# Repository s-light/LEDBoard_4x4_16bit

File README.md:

<!--lint disable maximum-line-length-->
<!--lint disable list-item-spacing-->
<!--lint disable list-item-indent-->

# LED-Board 4x4 16bit

a LED-Matrix Board that can be combined seamlessly to bigger areas.  
It uses the [TI TLC5971](http://www.ti.com/product/TLC5971) Constant-Current LED-Driver Chip with 16bit dimming resolution.  

The [original](https://github.com/s-light/LEDBoard_4x4_16bit/tree/Nichia_NSSM032A) LED-footprint was for [Nichia NSSM032A](http://www.nichia.co.jp/en/product/led_product_data.html?type=%27NSSM032A%27) RGB-LED.
Back in 2017 on of the brightest *low power* SMD LEDs in this size -
They are only available as full reel directly from Nichia.

so there is a [second branch](https://github.com/s-light/LEDBoard_4x4_16bit/tree/Nichia_NSSM124D) with the LED-Type changed to [Nichia NSSM124D](http://www.nichia.co.jp/en/product/led_product_data.html?type=%27NSSM124D%27) -
these are [available as cut-tape from an distributor](http://www.leds.de/en/Ordinary-LEDs/SMD-LEDs/Nichia-SMD-LED-RGB-NSSM124DT.html).

latest addition is a [branch with TLC5971*PWP* driver chips](https://github.com/s-light/LEDBoard_4x4_16bit/tree/TLC5971PWP) -
this is the same chip but in an HTSSOP-20 housing -
that is easier to solder by hand.
--> no hot air / reflow oven necessary, but recommend.

## Project-Status
- received first Batch ([Release V1.0.0](https://github.com/s-light/LEDBoard_4x4_16bit/releases/tag/v1.0))
- received second Batch ([Release V3.0.1](https://github.com/s-light/LEDBoard_4x4_16bit/tree/v3.0.1))
- 11 PCB's assembled  
  10 working :sun_with_face:  
  first solder board not working - has a short between VCC and GND (to be checked)
- all needed heavy rework: stencil has to big openings - this gives a bunch of bridges at QFN 0,5mm Pin-Pitch IC's
- had some problems with the first reflow oven used - you need enough heat from the bottom to solder correctly.
- made some picture from first assembly: [gallery](./doc/gallery.md)
- ~~fix pads that are to small for hand-soldering~~ done
- ~~order updated PCB's~~ done
- ~~solder some more boards~~ done (total: ~60)
- ~~order screws at [Wegertseder](https://www.wegertseder.com/ArticleDetails.aspx?AKNUM=2588)~~ done
- updated KiCad files to new version.

### TODO
- order Heat Sink with machining and Thermal Foil from [Fischer Elektronik](http://www.fischerelektronik.de/web_fischer/de_DE/K%C3%BChlk%C3%B6rper/B01/K%C3%BChlk%C3%B6rper%20f%C3%BCr%20PGA/PR/ICKPGA14x14x12_/$productCard/parameters/index.xhtml)
- add some more mounting layouts to [LEDBoard_Layouts](https://github.com/s-light/LEDBoard_Layouts)
- take some more pictures

## Technical Information
there are groups of 4 LEDs that are controlled by one TLC5971.  
every controller chip has 12 ConstantCurrent outputs. so every LED is controllable individual.

you need to create a mapping to linearize the order:  

| X/Y   | 0        | 1        | 2        | 3        |
| :---- | :------- | :------- | :------- | :------- |
| **0** | IC1 LED1 | IC1 LED2 | IC2 LED1 | IC2 LED2 |
| **1** | IC1 LED3 | IC1 LED4 | IC2 LED3 | IC2 LED4 |
| **2** | IC3 LED1 | IC3 LED2 | IC4 LED1 | IC4 LED2 |
| **3** | IC3 LED3 | IC3 LED4 | IC4 LED3 | IC4 LED4 |

example for c++ / arduino
```c++
const uint8_t channel_position_map[4][4] = {
    { 0,  1,  4,  5},
    { 2,  3,  6,  7},
    { 8,  9, 12, 13},
    {10, 11, 14, 15},
};
```

### HW
- PCB size: 40x40x18mm
- pixel-pitch: 10mm
- 3.8V..5.5V
- <= 1A (maximum)

### BOM
there is the raw exported BOM at [export/BOM/LEDBoard_4x4_16bit_BOM.csv](export/BOM/LEDBoard_4x4_16bit_BOM.csv) and an modified LibreOffice Calc file with ordering and Price calculations at [doc/LEDBoard_4x4_16bit_PriceCalculation_Ordering](doc/LEDBoard_4x4_16bit_PriceCalculation_Ordering.csv) (link points to exported csv as preview)

### controlling

#### Micro Controller / Arduino
there are some Arduino Libraries out there that can generate the correct protocol.
My Favorite is [ulrichstern/Tlc59711](https://github.com/ulrichstern/Tlc59711)

i have made a [simple arduino sketch](https://github.com/s-light/LEDBoard_4x4_16bit_HWTest) that uses the mentioned library to test the Boards during production.

#### embedded linux boards
Additionally you can use a embedded Linux board with an SPI output to drive them.
I have successfully implemented the protocol in my fork of OLA.
(TODO: Link and explain OLA setup)

there are also other python libraries out there.
(TODO: test some of theme and link here)

### power & signal connections
theoretically calculate with about 1A@5V for every Board.
Supply Voltage (VCC) should be 3,8V..5,5V - If possible use the lower end. so no extra heat is generated in the driver IC.

for the control-signal there are an input and output 3pin 2,54mm connector:
1. Data
1. Clock
1. GND

for the power there are 3x2pin 2,54mm connector positions.
so you could daisy-chain power also - but be aware the pcb-traces can handle an absolute maximum of 3,5A. So i would recommend only 1 or maximum 2 daisy-chained boards.

## KiCad Version
```text
Application: KiCad

Version: 5.99.0-unknown-652a59b78~104~ubuntu20.04.1, release build

Libraries:
	wxWidgets 3.0.4
	libcurl/7.68.0 OpenSSL/1.1.1f zlib/1.2.11 brotli/1.0.7 libidn2/2.2.0 libpsl/0.21.0 (+libidn2/2.2.0) libssh/0.9.3/openssl/zlib nghttp2/1.40.0 librtmp/2.3

Platform: Linux 5.4.0-48-generic x86_64, 64 bit, Little endian, wxGTK

Build Info:
	Date: Sep 16 2020 10:16:55
	wxWidgets: 3.0.4 (wchar_t,wx containers,compatible with 2.8) GTK+ 3.24
	Boost: 1.71.0
	OCE: 6.9.1
	Curl: 7.68.0
	ngspice: 31
	Compiler: GCC 9.3.0 with C++ ABI 1013

Build settings:
	KICAD_SCRIPTING=ON
	KICAD_SCRIPTING_MODULES=ON
	KICAD_SCRIPTING_PYTHON3=ON
	KICAD_SCRIPTING_WXPYTHON=ON
	KICAD_SCRIPTING_WXPYTHON_PHOENIX=ON
	KICAD_SCRIPTING_ACTION_MENU=ON
	BUILD_GITHUB_PLUGIN=ON
	KICAD_USE_OCE=ON
	KICAD_SPICE=ON

```

## License
<!-- License info -->
<br />
<span xmlns:dct="http://purl.org/dc/terms/" property="dct:title">
    LEDBoard_4x4_16bit
</span>
by
<a xmlns:cc="http://creativecommons.org/ns#" href="https://github.com/s-light/LEDBoard_4x4_16bit" property="cc:attributionName" rel="cc:attributionURL">
    Stefan Krüger (s-light)
</a>
is licensed under a
<a rel="license" href="http://creativecommons.org/licenses/by/4.0/">
    Creative Commons Attribution 4.0 International License
</a>.

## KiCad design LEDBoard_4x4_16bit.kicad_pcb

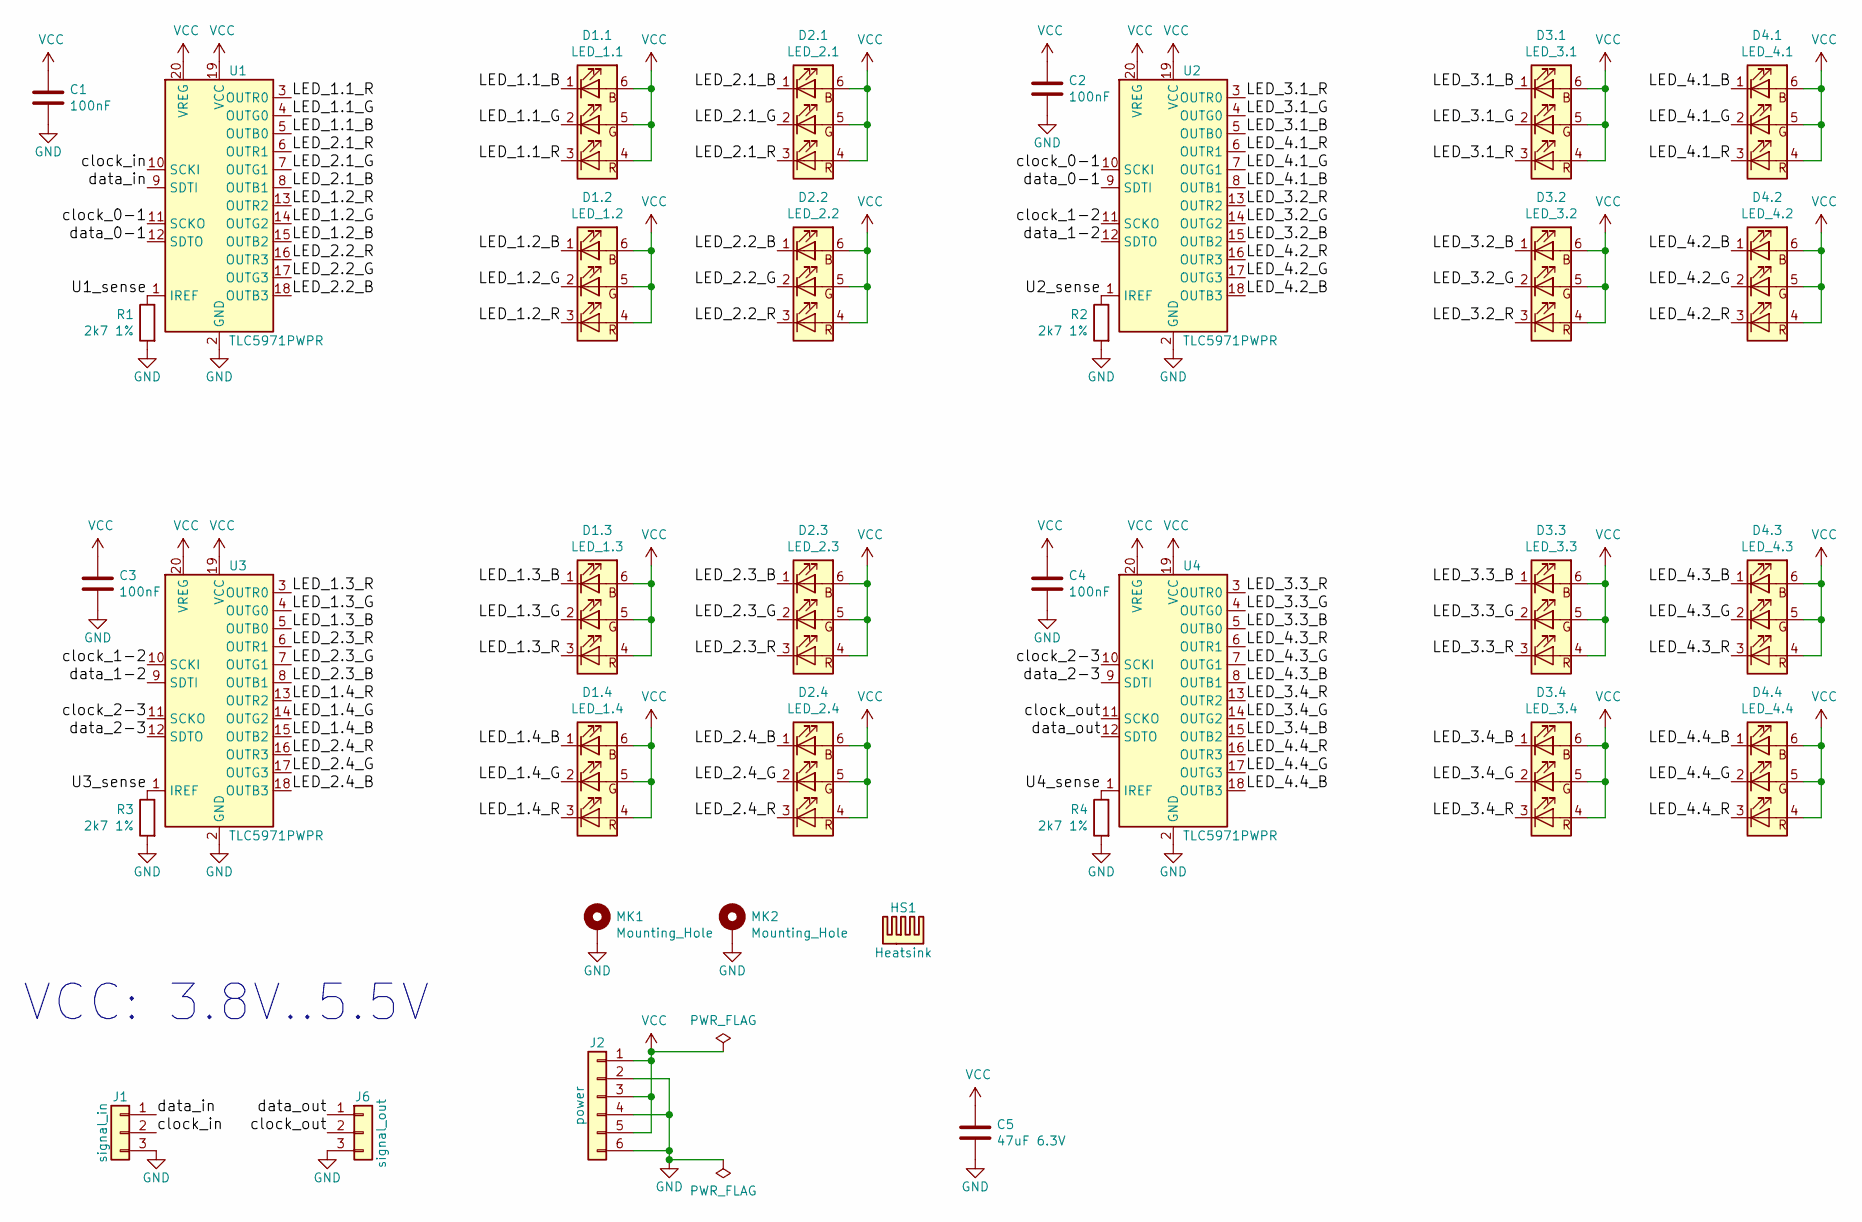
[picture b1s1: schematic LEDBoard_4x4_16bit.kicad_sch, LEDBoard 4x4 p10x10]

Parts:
C1, C2, C3, C4: 100nF; C_0603_HandSoldering; mouser 81-GRM39X104K50D
C5: 47uF 6.3V; C_0603_HandSoldering; mouser 81-GRM188R60J476ME5D
D1.1: LED_1.1; LED_NSSM124_wViaHeatSinkBig_roundedPads
D1.2: LED_1.2; LED_NSSM124_wViaHeatSinkBig_roundedPads
D1.3: LED_1.3; LED_NSSM124_wViaHeatSinkBig_roundedPads
D1.4: LED_1.4; LED_NSSM124_wViaHeatSinkBig_roundedPads
D2.1: LED_2.1; LED_NSSM124_wViaHeatSinkBig_roundedPads
D2.2: LED_2.2; LED_NSSM124_wViaHeatSinkBig_roundedPads
D2.3: LED_2.3; LED_NSSM124_wViaHeatSinkBig_roundedPads
D2.4: LED_2.4; LED_NSSM124_wViaHeatSinkBig_roundedPads
D3.1: LED_3.1; LED_NSSM124_wViaHeatSinkBig_roundedPads
D3.2: LED_3.2; LED_NSSM124_wViaHeatSinkBig_roundedPads
D3.3: LED_3.3; LED_NSSM124_wViaHeatSinkBig_roundedPads
D3.4: LED_3.4; LED_NSSM124_wViaHeatSinkBig_roundedPads
D4.1: LED_4.1; LED_NSSM124_wViaHeatSinkBig_roundedPads
D4.2: LED_4.2; LED_NSSM124_wViaHeatSinkBig_roundedPads
D4.3: LED_4.3; LED_NSSM124_wViaHeatSinkBig_roundedPads
D4.4: LED_4.4; LED_NSSM124_wViaHeatSinkBig_roundedPads
HS1: Heatsink; Dummy_Empty
J1: signal_in; Socket_Strip_Straight_1x03_Pitch2.54mm
J2: power; Socket_Strip_Straight_1x06_Pitch2.54mm
J6: signal_out; Socket_Strip_Straight_1x03_Pitch2.54mm
MK1, MK2: Mounting_Hole; MountingHole_3.2mm_M3_ISO7380_Pad
R1, R2, R3, R4: 2k7 1%; R_0603_HandSoldering; mouser 71-CRCW06032K70FKEB
U1, U2, U4: TLC5971PWPR; HTSSOP-20-1EP_4.4x6.5mm_P0.65mm_EP3.4x6.5mm_Mask2.75x3.43mm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; mouser 595-TLC5971PWPR
U3: TLC5971PWPR; HTSSOP-20-1EP_4.4x6.5mm_Pitch0.65mm_ThermalVias_TI_R-PDSO-G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; mouser 595-TLC5971PWPR

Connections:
/LED_1.1_B: D1.1.1 (RK), U1.5 (OUTB0)
/LED_1.1_G: D1.1.2 (GK), U1.4 (OUTG0)
/LED_1.1_R: D1.1.3 (BK), U1.3 (OUTR0)
/LED_1.2_B: D1.2.1 (RK), U1.15 (OUTB2)
/LED_1.2_G: D1.2.2 (GK), U1.14 (OUTG2)
/LED_1.2_R: D1.2.3 (BK), U1.13 (OUTR2)
/LED_1.3_B: D1.3.1 (RK), U3.5 (OUTB0)
/LED_1.3_G: D1.3.2 (GK), U3.4 (OUTG0)
/LED_1.3_R: D1.3.3 (BK), U3.3 (OUTR0)
/LED_1.4_B: D1.4.1 (RK), U3.15 (OUTB2)
/LED_1.4_G: D1.4.2 (GK), U3.14 (OUTG2)
/LED_1.4_R: D1.4.3 (BK), U3.13 (OUTR2)
/LED_2.1_B: D2.1.1 (RK), U1.8 (OUTB1)
/LED_2.1_G: D2.1.2 (GK), U1.7 (OUTG1)
/LED_2.1_R: D2.1.3 (BK), U1.6 (OUTR1)
/LED_2.2_B: D2.2.1 (RK), U1.18 (OUTB3)
/LED_2.2_G: D2.2.2 (GK), U1.17 (OUTG3)
/LED_2.2_R: D2.2.3 (BK), U1.16 (OUTR3)
/LED_2.3_B: D2.3.1 (RK), U3.8 (OUTB1)
/LED_2.3_G: D2.3.2 (GK), U3.7 (OUTG1)
/LED_2.3_R: D2.3.3 (BK), U3.6 (OUTR1)
/LED_2.4_B: D2.4.1 (RK), U3.18 (OUTB3)
/LED_2.4_G: D2.4.2 (GK), U3.17 (OUTG3)
/LED_2.4_R: D2.4.3 (BK), U3.16 (OUTR3)
/LED_3.1_B: D3.1.1 (RK), U2.5 (OUTB0)
/LED_3.1_G: D3.1.2 (GK), U2.4 (OUTG0)
/LED_3.1_R: D3.1.3 (BK), U2.3 (OUTR0)
/LED_3.2_B: D3.2.1 (RK), U2.15 (OUTB2)
/LED_3.2_G: D3.2.2 (GK), U2.14 (OUTG2)
/LED_3.2_R: D3.2.3 (BK), U2.13 (OUTR2)
/LED_3.3_B: D3.3.1 (RK), U4.5 (OUTB0)
/LED_3.3_G: D3.3.2 (GK), U4.4 (OUTG0)
/LED_3.3_R: D3.3.3 (BK), U4.3 (OUTR0)
/LED_3.4_B: D3.4.1 (RK), U4.15 (OUTB2)
/LED_3.4_G: D3.4.2 (GK), U4.14 (OUTG2)
/LED_3.4_R: D3.4.3 (BK), U4.13 (OUTR2)
/LED_4.1_B: D4.1.1 (RK), U2.8 (OUTB1)
/LED_4.1_G: D4.1.2 (GK), U2.7 (OUTG1)
/LED_4.1_R: D4.1.3 (BK), U2.6 (OUTR1)
/LED_4.2_B: D4.2.1 (RK), U2.18 (OUTB3)
/LED_4.2_G: D4.2.2 (GK), U2.17 (OUTG3)
/LED_4.2_R: D4.2.3 (BK), U2.16 (OUTR3)
/LED_4.3_B: D4.3.1 (RK), U4.8 (OUTB1)
/LED_4.3_G: D4.3.2 (GK), U4.7 (OUTG1)
/LED_4.3_R: D4.3.3 (BK), U4.6 (OUTR1)
/LED_4.4_B: D4.4.1 (RK), U4.18 (OUTB3)
/LED_4.4_G: D4.4.2 (GK), U4.17 (OUTG3)
/LED_4.4_R: D4.4.3 (BK), U4.16 (OUTR3)
/U1_sense: R1.1, U1.1 (IREF)
/U2_sense: R2.1, U2.1 (IREF)
/U3_sense: R3.1, U3.1 (IREF)
/U4_sense: R4.1, U4.1 (IREF)
/clock_0-1: U1.11 (SCKO), U2.10 (SCKI)
/clock_1-2: U2.11 (SCKO), U3.10 (SCKI)
/clock_2-3: U3.11 (SCKO), U4.10 (SCKI)
/clock_in: J1.2, U1.10 (SCKI)
/clock_out: J6.2, U4.11 (SCKO)
/data_0-1: U1.12 (SDTO), U2.9 (SDTI)
/data_1-2: U2.12 (SDTO), U3.9 (SDTI)
/data_2-3: U3.12 (SDTO), U4.9 (SDTI)
/data_in: J1.1, U1.9 (SDTI)
/data_out: J6.1, U4.12 (SDTO)
GND: C1.2, C2.2, C3.2, C4.2, C5.2, J1.3, J2.2, J2.4, J2.6, J6.3, MK1.1, MK2.1, R1.2, R2.2, R3.2, R4.2, U1.2 (GND), U1.21 (GND), U2.2 (GND), U2.21 (GND), U3.2 (GND), U3.21 (GND), U4.2 (GND), U4.21 (GND)
VCC: C1.1, C2.1, C3.1, C4.1, C5.1, D1.1.4 (BA), D1.1.5 (GA), D1.1.6 (RA), D1.2.4 (BA), D1.2.5 (GA), D1.2.6 (RA), D1.3.4 (BA), D1.3.5 (GA), D1.3.6 (RA), D1.4.4 (BA), D1.4.5 (GA), D1.4.6 (RA), D2.1.4 (BA), D2.1.5 (GA), D2.1.6 (RA), D2.2.4 (BA), D2.2.5 (GA), D2.2.6 (RA), D2.3.4 (BA), D2.3.5 (GA), D2.3.6 (RA), D2.4.4 (BA), D2.4.5 (GA), D2.4.6 (RA), D3.1.4 (BA), D3.1.5 (GA), D3.1.6 (RA), D3.2.4 (BA), D3.2.5 (GA), D3.2.6 (RA), D3.3.4 (BA), D3.3.5 (GA), D3.3.6 (RA), D3.4.4 (BA), D3.4.5 (GA), D3.4.6 (RA), D4.1.4 (BA), D4.1.5 (GA), D4.1.6 (RA), D4.2.4 (BA), D4.2.5 (GA), D4.2.6 (RA), D4.3.4 (BA), D4.3.5 (GA), D4.3.6 (RA), D4.4.4 (BA), D4.4.5 (GA), D4.4.6 (RA), J2.1, J2.3, J2.5, U1.19 (VCC), U1.20 (VREG), U2.19 (VCC), U2.20 (VREG), U3.19 (VCC), U3.20 (VREG), U4.19 (VCC), U4.20 (VREG)

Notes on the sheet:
VCC: 3.8V..5.5V

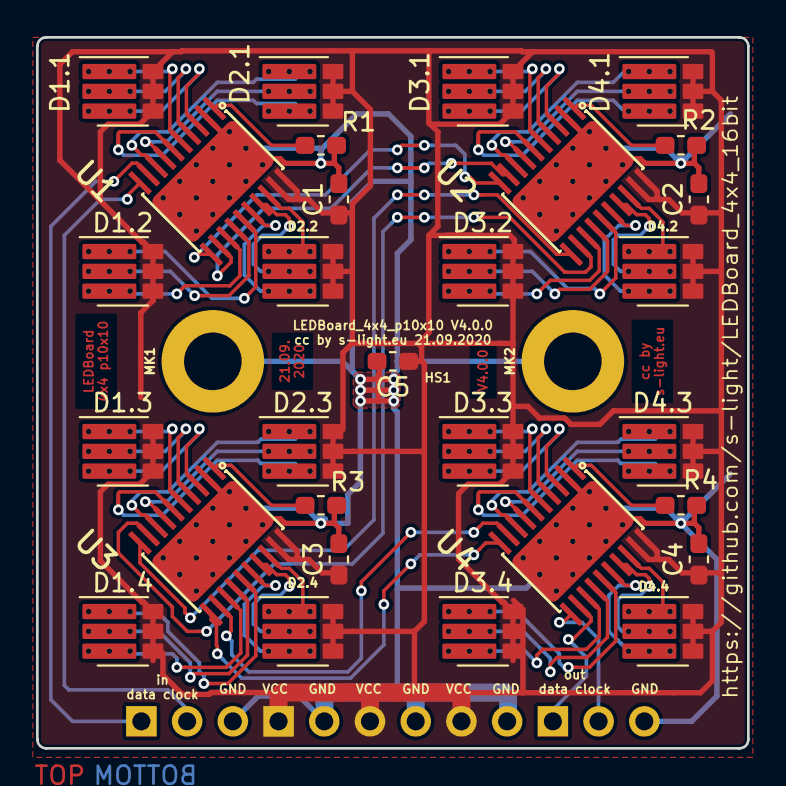
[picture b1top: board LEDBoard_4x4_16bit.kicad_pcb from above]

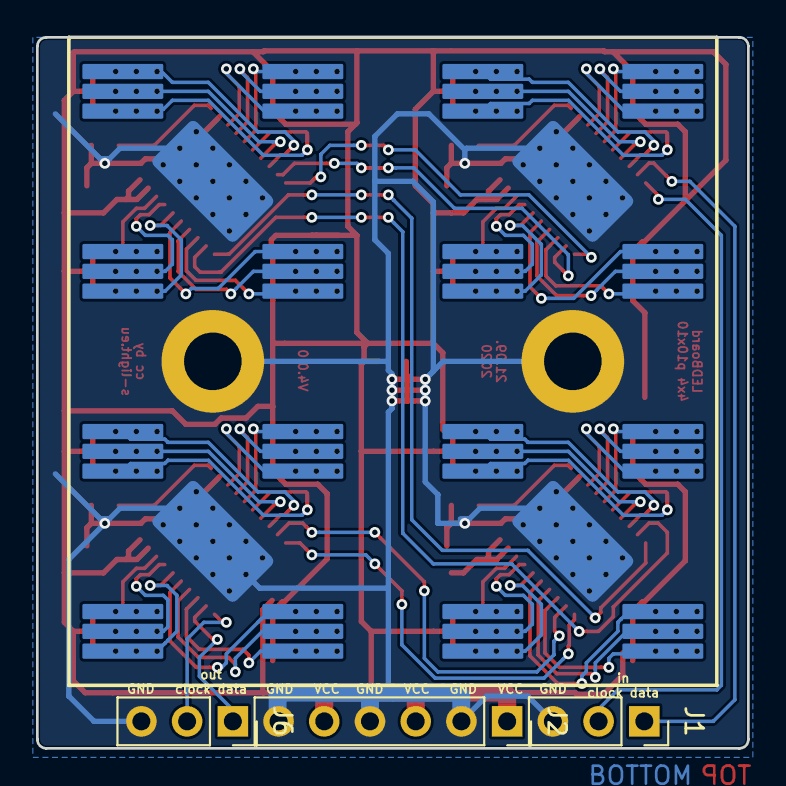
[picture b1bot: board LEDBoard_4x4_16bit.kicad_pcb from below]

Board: 2 copper layers, 39.5 x 39.5 mm, 35 parts (4 on the bottom side), 64 nets.

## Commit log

2017-07-13 added schematic + basic pcb layout
2017-07-16 pcb parts all positioned
2017-07-17 pcb started routing
2017-07-17 pcb routing almost finished
2017-07-17 pcb tried to fix missing net links
2017-07-17 updated net labeling
2017-07-17 pcb fixed broken net data_2-3
2017-07-17 fixed net data_1-2 (manually hand edited net-file)
2017-07-17 fixed screw 3D-model
2017-07-17 pcb added heatsink 3d model
2017-07-17 generated images
2017-07-17 pcb generated images backside
2017-07-17 pcb updated page title block
2017-07-17 README update added * Project-Status * Technical Information * description * HW * controlling * power / signal connections * KiCad Version
2017-07-18 pcb exported gerber
2017-07-18 pcb updated gerber files to work with go.aisler.net
2017-07-18 README updated status
2017-07-18 drawing for mechanical parts created
2017-07-31 updated things
2017-07-31 updated gerber files
2017-07-31 :memo: added BOM & Price/Ordering Calculations
2017-07-31 added export svg & pdf
2017-07-31 :sunrise: added images from production
2017-07-31 added assembly image gallery
2017-08-02 :memo: hopefully fixed csv file
2017-08-02 :memo: regenerate csv now text should be quoted so it can be interpreted by github for rendering :-)
2017-08-02 :memo: added missing part numbers mostly to get a consisten row count in the exported BOM csv file
2017-08-03 schematic: changed signal in & signal out to 3pin connector
2017-08-03 :memo: fixed netlist manually removed buggy double pin 6 entries
2017-08-03 updated pcb to use new connector layout
2017-08-03 generated gerber files
2017-08-03 updated version info in pcb
2017-08-03 generated exports
2017-08-03 pcb fixed comment
2017-08-03 :memo: updated README
2017-08-08 pcb: changed size and corners. size: to allow for 0,5mm tolerance corners: minimal radius 0,5mm
2017-08-08 added soldering profile info (combined from the nichia and Felder datasheets)
2017-08-08 schematic: updated LED-Type to NSSM124D + generated BOM + exported NET-List + modified it (changed buggy nets)
2017-08-09 updated pcb to LED-Type NSSM124D
2017-08-09 pcb updated renderings
2017-08-09 updated exports
2017-08-09 pcb footprints: updated 3D-Models to use step
2017-08-09 generated 3D-Model step file
2017-08-30 :rainbow: added image with two pcbs working
2017-08-30 :rainbow: updated gallery
2017-08-30 started to do variant with TLC5971PWP --> HTSSOP housing
2017-08-31 preparation for new housings
2017-08-31 updated driver housings + reroute
2017-08-31 updated BOM
2017-08-31 updated exports and images
2017-09-04 pcb: temporary remove layer-alignment-target
2017-09-04 updated PriceCalculation
2017-09-20 v2.0.2 fixed Stencil/Solder-Paste openings for QFN drivers; +full export
2017-09-21 added step file
2017-09-22 experimental manual rounding of all smd pads
2017-09-22 pcb update export
2017-09-23 added reflow tests/log information
2017-09-27 updated smd pads to roundedrect version
2017-11-17 update reflow soldering info
2017-11-30 removed solidworks ignores
2017-12-05 updated readme ;-)
2017-12-10 updated board-count
2017-12-16 fixed ProjectStatus Paragraph
2017-12-16 updated schematic to new file format
2017-12-16 updated Resistors and Capacitors for easier handsoldering
2018-01-19 updated HeatSink Mounting
2018-02-08 updated todo list
2018-02-09 partly updated pcb
2018-02-09 updated renderings
2018-02-09 fixed virtual components
2018-02-09 updated exported step
2018-02-09 updated version info
2018-02-09 changed gridorigin to center of pcb & reexported step
2020-09-20 update HeatSink infos
2020-09-20 update HeatSink infos
    (cherry picked from commit 1320d880c5138aec875839203008c73e6e43c43f)
2020-09-21 update Schematics & PCB to - kicad nightliy 599 - use current default librarie symbols and footprints - create renderings

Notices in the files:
LEDBoard_4x4_16bit.kicad_pcb:
cc by
cc by s-light.eu 21.09.2020
LEDBoard_4x4_16bit.kicad_sch:
license: CC BY
